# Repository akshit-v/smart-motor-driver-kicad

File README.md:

# Smart-Motor-Driver-kicad
A high-efficiency 60V/40A smart motor driver with real-time current and voltage sensing, reverse polarity protection, and a cost-optimized PCB design
Smart Motor Driver – Kicad

This repository contains the complete design and documentation for a smart motor driver capable of driving two high-current DC motors (up to 60V, 40A each) with real-time voltage and current sensing. The driver is built using discrete components, and gate drivers for H-bridge MOSFET control. It is designed for high-efficiency operation, integrated protection, and microcontroller-based control.

The project includes the full schematic, PCB layout, firmware interface, and performance analysis. It is intended for embedded system applications such as robotics, automation, and motorized systems requiring efficient and protected motor drive control.

---
# Project Features
- **Dual Channel Motor Drive**: Two independent H-Bridge circuits with dedicated gate drivers.
- **High Voltage and Current Support**: Operates at up to 60V input and handles continuous motor current up to 40A per channel.
- **High Efficiency**: Optimized gate drive timing, low-loss power MOSFETs, and minimized switching losses provide efficiency above 90% under load.
- **Current and Voltage Feedback**: Op-amp-based analog sensing circuits for real-time current and voltage monitoring with ±1% accuracy.
- **Reverse Polarity Protection**: Input protection circuit safeguards the board from accidental reverse connections.
- **Microcontroller Interface**: PWM-compatible logic-level inputs for speed and direction control 
- **Integrated Voltage Regulation**: Onboard buck regulators generate 5V and 3.3V rails for logic and sensors.
- **USB-to-Serial Interface**: Using a USB-to-Serial converter (CH340-C) for real-time data logging, motor control, and firmware debugging via serial terminal.
- **Modular Design**: Separated sections for control logic, power stages, sensing, and regulation.

---

## Schematic Highlights

- **Power Section**: Includes reverse polarity protection, input filtering, and buck converters (AP63205WU, AP7316-C) for 5V and 3.3V rails.
- **Gate Drivers**: MC33883 used to drive the high- and low-side N-channel MOSFETs for each H-bridge.
- **Motor Channels**: Two H-Bridge configurations, each with four MOSFETs and flyback diodes for inductive protection.
- **Current Sensing**: Differential amplifier circuits with op-amps (LM358) for low-side current sensing on each motor.
- **Voltage Monitoring**: Voltage divider and op-amp buffer stages for voltage feedback to the controller.
- **Microcontroller Interface**: PWM signal lines, direction pins, and feedback outputs prepared for logic-level interfacing.

---

## Tools and Components Used

- **Schematic & PCB Design**: KiCad
- **Analog Simulation**: Proteus
- **Gate Driver**: MC33883
- **Microcontroller Target**: ESP32
- **Op-Amps**: LM358 (for current and voltage sensing)
- **MOSFETs**: N-channel high-current rated, low Rds(on)
- **Voltage Regulators**: AP63205WU, AP7316-C for 5V and 3.3V and 74HCT244 for level shifting
- **Other Tools**: Proteus (for logic testing), T-Cad (device simulation reference)

---

## Applications

- Custom embedded robotic platforms
- Industrial or academic motor control systems

---

## Performance Summary

- **Efficiency**: >90% at full load
- **Current Measurement Error**: ±1% (tested using calibrated load)
- **MOSFET Temperature Rise**: Within safe limits under continuous 30A drive with proper heat dissipation
- **Cost**: 40% lower than comparable commercial motor drivers with similar specs

---
[View Schematic (PDF)](Schematic.pdf)
---

---

---

---

---

---

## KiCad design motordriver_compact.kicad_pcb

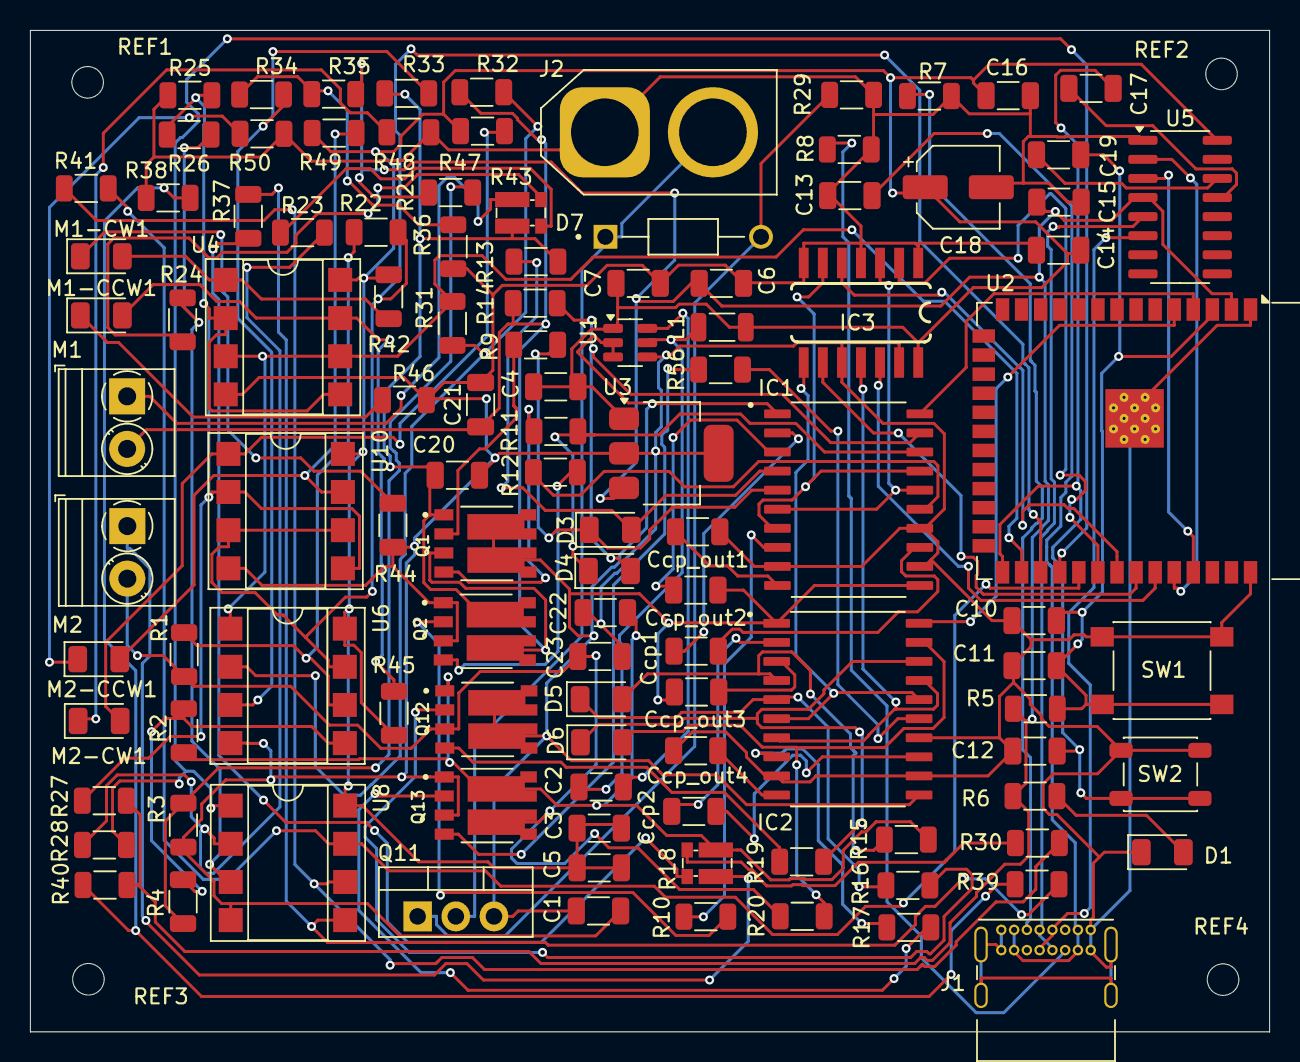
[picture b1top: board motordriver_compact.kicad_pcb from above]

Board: 2 copper layers, 82.5 x 66.7 mm, 115 parts (0 on the bottom side), 92 nets.

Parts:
C1: 10uF; C_1206_3216Metric
C2, C5, C11, C12: 0.1uF; C_1206_3216Metric
C3, C4: 22uF; C_1206_3216Metric
C6, C7: 4.7uF; C_1206_3216Metric
C10, C16: 1uF; C_1206_3216Metric
C13, C14, C17, C19: 100nF; C_1206_3216Metric
C15, C20, C21, C22, C23: 10nF; C_1206_3216Metric
C18: 10uF; CP_Elec_5x3
Ccp1, Ccp2: 33nF; C_1206_3216Metric
Ccp_out1, Ccp_out2, Ccp_out3, Ccp_out4: 470nF; C_1206_3216Metric
D1: LED; LED_1206_3216Metric
D3, D4, D5, D6: D_Schottky_Small; D_1206_3216Metric
D7: 1N4740A; DIOAD1036W78L463D272
IC1, IC2: MC33883HEG; SOIC127P1030X265-20N
IC3: 74HC125; SOIC-14
J1: USB_C_Receptacle_USB2.0_14P; USB_C_Receptacle_GCT_USB4085
J2: Conn_01x02_Socket; AMASS_XT60-M_1x02_P7.20mm_Vertical
L1: 4.7uH; L_1206_3216Metric
M1, M2: Motor_DC; TerminalBlock_Phoenix_PT-1,5-2-3.5-H_1x02_P3.50mm_Horizontal
M1-CCW1, M1-CW1, M2-CCW1, M2-CW1: LED; LED_1206_3216Metric
Q1, Q2, Q12, Q13: TQM076NH04LDCR_RLG; TRANS_TQM076NH04LDCR_RLG
Q11: IRF4905; TO-220-3_Vertical
R1, R2, R3, R21, R23, R24, R25, R27, R29, R30, R32, R33, R35, R36, R37, R38, R40: 10k; R_1206_3216Metric
R4, R22, R26, R28, R31, R34, R39, R41: 275; R_1206_3216Metric
R5: 10K; R_1206_3216Metric
R6, R9, R10, R11, R12, R16, R17, R19, R56: 50; R_1206_3216Metric
R7, R8: 5k; R_1206_3216Metric
R13, R14, R15, R20: 10; R_1206_3216Metric
R18, R43: 01m; R_Shunt_Vishay_WSKW0612
R42, R45, R47, R49: 470; R_1206_3216Metric
R44, R46, R48, R50: 100; R_1206_3216Metric
REF1, REF2, REF3, REF4: MountingHole_2.1mm
SW1: SW_SPST; SW_SPST_PTS645
SW2: SW_SPST; SW_SPST_PTS647_Sx38
U1: AP63205WU; TSOT-23-6
U2: ESP32-S3-WROOM-1
U3: AP7361C-33E; SOT-223-3_TabPin2
U4, U10: LM393; DIP-8_W7.62mm_SMDSocket_SmallPads
U5: CH340C; SOIC-16_3.9x9.9mm_P1.27mm
U6, U8: LM358; DIP-8_W7.62mm_SMDSocket_SmallPads

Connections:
+3.3V: C6.1, C15.1, R5.1, R6.1, R21.2, R27.2, R35.2, R40.2, U2.2 (3V3), U3.3 (VO), U5.4 (V3)
+5V: C3.1, C3.2, C4.1, C4.2, C5.1, C5.2, C7.1, C14.2, C16.1, C18.1, IC3.14 (VCC), L1.2, R42.1, R45.1, R47.1, R49.1, U1.1 (FB), U3.1 (VI), U4.8 (V+), U5.16 (VCC), U6.8 (V+), U8.8 (V+), U10.8 (V+)
+BATT: C1.1, Ccp_out2.1, Ccp_out3.1, IC1.1 (VCC), IC1.11 (VCC2), IC2.1 (VCC), IC2.11 (VCC2), Q1.5_6, Q1.7_8, Q11.3 (S), Q12.5_6, Q12.7_8, U1.2 (EN), U1.3 (IN)
/1.65V: R25.2, R26.1, R27.1, U4.2 (-), U4.5 (+), U10.2 (-), U10.5 (+)
/4: IC1.20 (G_EN), U2.4 (IO4)
/5: IC2.20 (G_EN), U2.5 (IO5)
/C1': Ccp1.2, IC1.13 (C1)
/C1'': Ccp2.2, IC2.13 (C1)
/C2': Ccp1.1, IC1.2 (C2)
/C2'': Ccp2.1, IC2.2 (C2)
/C_sense1: R28.2, U2.30 (IO37), U8.1
/C_sense2: R41.2, U2.31 (IO38), U8.7
/DTR: C12.2, C17.2, SW2.2 (B), U2.27 (IO0)
/GATE_HS1: D3.1 (K), IC1.5 (GATE_HS1), R9.1
/GATE_HS1': D5.1 (K), IC2.5 (GATE_HS1), R16.1
/GATE_HS2: D4.1 (K), IC1.18 (GATE_HS2), R11.2
/GATE_HS2': D6.1 (K), IC2.18 (GATE_HS2), R19.2
/GATE_LS1: IC1.8 (GATE_LS1), R10.1
/GATE_LS1': IC2.8 (GATE_LS1), R17.1
/GATE_LS2: IC1.15 (GATE_LS2), R12.1
/GATE_LS2': IC2.15 (GATE_LS2), R56.1
/M39: IC3.2 (1A), U2.32 (IO39)
/M39_5V: IC1.6 (IN_HS1), IC1.16 (IN_LS2), IC3.3 (1Y)
/M40: IC3.5 (2A), U2.33 (IO40)
/M40_5V: IC1.7 (IN_LS1), IC1.17 (IN_HS2), IC3.6 (2Y)
/M41: IC3.9 (3A), U2.34 (IO41)
/M41_5V: IC2.6 (IN_HS1), IC2.16 (IN_LS2), IC3.8 (3Y)
/M42: IC3.12 (4A), U2.35 (IO42)
/M42_5V: IC2.7 (IN_LS1), IC2.17 (IN_HS2), IC3.11 (4Y)
/RTS: C10.2, C11.2, C19.2, R5.2, SW1.2 (B), U2.3 (EN)
/SRC_HS1: D3.2 (A), IC1.4 (SRC_HS1), R13.1
/SRC_HS1': D5.2 (A), IC2.4 (SRC_HS1), R15.1
/SRC_HS2: D4.2 (A), IC1.19 (SRC_HS2), R14.2
/SRC_HS2': D6.2 (A), IC2.19 (SRC_HS2), R20.2
/UART_RX: U2.37 (TXD0), U5.3 (RXD)
/UART_TX: U2.36 (RXD0), U5.2 (TXD)
/V_cur1+: R24.1, R43.2
/V_cur1-: R23.1, R43.3
/V_cur2+: R18.2, R37.1
/V_cur2-: R18.3, R30.1
/V_sense1: R31.2, U2.28 (IO35), U4.3 (+), U4.6 (-), U6.1
/V_sense2: R22.2, U2.29 (IO36), U6.7, U10.3 (+), U10.6 (-)
/Vmot1_CCW: C21.1, M1.2 (-), Q1.3, Q2.5_6, R14.1, R32.1
/Vmot1_CW: C20.2, Q1.1, Q2.7_8, R13.2, R33.1, R43.4
/Vmot2_CCW: C23.1, M2.2 (-), Q12.3, Q13.5_6, R1.1, R20.1
/Vmot2_CW: C22.2, Q12.1, Q13.7_8, R2.1, R15.2, R18.4
/usb_5v: C13.2, J1.A4 (VBUS), J1.A9 (VBUS), J1.B4 (VBUS), J1.B9 (VBUS)
GND: C1.2, C6.2, C7.2, C10.1, C11.1, C12.1, C13.1, C14.1, C15.2, C16.2, C18.2, C20.1, C21.2, C22.1, C23.2, Ccp_out1.1, Ccp_out4.1, D1.1 (K), IC1.9 (GND1), IC1.12 (GND_A), IC1.14 (GND2), IC2.9 (GND1), IC2.12 (GND_A), IC2.14 (GND2), IC3.1 (1OE), IC3.4 (2OE), IC3.7 (GND), IC3.10 (3OE), IC3.13 (4OE), J1.A1 (GND), J1.A12 (GND), J1.B1 (GND), J1.B12 (GND), J1.S1 (SHIELD), J2.1, Q2.1, Q2.3, Q13.1, Q13.3, R3.1, R7.2, R8.2, R25.1, R29.2, R36.1, R38.1, R44.2, R46.2, R48.2, R50.2, SW1.1 (A), SW2.1 (A), U1.4 (GND), U2.1 (GND), U2.40 (GND), U2.41 (GND), U3.2 (GND), U4.4 (V-), U5.1 (GND), U6.4 (V-), U8.4 (V-), U10.4 (V-)
unnamed: D1.2 (A), R6.2
unnamed: Ccp_out2.2, IC1.3 (CP_OUT)
unnamed: Ccp_out1.2, IC1.10 (LR_OUT)
unnamed: Ccp_out3.2, IC2.3 (CP_OUT)
unnamed: Ccp_out4.2, IC2.10 (LR_OUT)
unnamed: J1.A5 (CC1), R7.1
unnamed: J1.B5 (CC2), R8.1
unnamed: D7.1, J2.2, Q11.2 (D)
unnamed: M1.1 (+), R43.1
unnamed: M1-CCW1.2 (A), R45.2, U4.7
unnamed: M1-CCW1.1 (K), R46.1
unnamed: M1-CW1.2 (A), R42.2, U4.1
unnamed: M1-CW1.1 (K), R44.1
unnamed: M2.1 (+), R18.1
unnamed: M2-CCW1.2 (A), R49.2, U10.7
unnamed: M2-CCW1.1 (K), R50.1
unnamed: M2-CW1.2 (A), R47.2, U10.1
unnamed: M2-CW1.1 (K), R48.1
unnamed: Q1.2, R9.2
unnamed: Q1.4, R11.1
unnamed: Q2.2, R10.2
unnamed: Q2.4, R12.2
unnamed: D7.2, Q11.1 (G), R29.1
unnamed: Q12.2, R16.2
unnamed: Q12.4, R19.1
unnamed: Q13.2, R17.2
unnamed: Q13.4, R56.2
unnamed: R3.2, R4.1, R21.1
unnamed: R34.1, R35.1, R36.2
unnamed: R38.2, R39.1, R40.1
unnamed: C2.2, U1.6 (BST)
unnamed: C2.1, L1.1, U1.5 (SW)
unnamed: J1.A6 (D+), J1.B6 (D+), U5.5 (UD+)
unnamed: J1.A7 (D-), J1.B7 (D-), U5.6 (UD-)
unnamed: C17.1, U5.13 (~DTR)
unnamed: C19.1, U5.14 (~RTS)
unnamed: R33.2, R34.2, U6.3 (+)
unnamed: R31.1, R32.2, U6.2 (-)
unnamed: R2.2, R4.2, U6.5 (+)
unnamed: R1.2, R22.1, U6.6 (-)
unnamed: R24.2, R26.2, U8.3 (+)
unnamed: R23.2, R28.1, U8.2 (-)
unnamed: R37.2, R39.2, U8.5 (+)
unnamed: R30.2, R41.1, U8.6 (-)
